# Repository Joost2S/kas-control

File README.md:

# kas-control
Kas Control is a Raspberry Pi expansion board for watering plants and checking a few more environmental variables
PCB should be correct.
Software is currently not functional. Use v2017 for basic functionality.

Features
--------
- PCB plugs straight into your rPi. rPi is powered through the PCB
- Measuring soil moisture level of up to 7 plants/containers
  - Can pump water to plant/container when moisture level is below threshold so you don't have to!
- Measuring amount of water given per channel and total
- Default 3 temperature sensors are supported by the board. Software supports infinite sensors. Make a simple breakout (connect parallel) board for more sensors.
- Light sensor for ambient light measurement.
- Float switch for use in a water container.
- Outputs:
  - 2 configurable LEDbars.
  - Standard HD44780 16x2 or 20x4 character LCD with driver kindly copied from ADAfruit.
- Network client to set the various setting and get the data.
  - Command-line only. Graph makes a Google graph html file that will open in a new tab in your browser
  - Basic encryption is implemented with openSSL
- Database
  - All sensor data is logged
  - Add a name and plant type to keep track of which plants you've grown
- 5v/12v 4A PSU PCB with INA219 power monitor. PCB files are available, haven't tested it yet.
  - 4 powerLED connectors are available for 350/500/700mA powerLED strips.
  - Power monitoring is available via INA219 ICs
  
Future Features
---------------
- Network
  - Full-fledged GUI for the network client. Probably built on Kivy.
  - rPi camera support so you can watch your plants from all over the world
- Database
  - Adding results such as plant size or harvest amount to each of your plants. Manual input only of course.
- Implement event system

Motivation
----------

I like weed. I like electronics. I like programming. Here's the result :)

Installation/requirements
-------------------------

- I use Arch Linux so only instructions for that. Actual instructions will follow later.
- RPi.GPIO
- SMBus for i2c
- spidev for SPI
- SQlite for database
- Kivy (future)

Contributors
------------

Sorry, no help wanted. This is my pet project and I want it to be just how I like it. Of Course you are welcome to use the code and pcb files as you wish.

License
-------

GNU General Public License v3.0

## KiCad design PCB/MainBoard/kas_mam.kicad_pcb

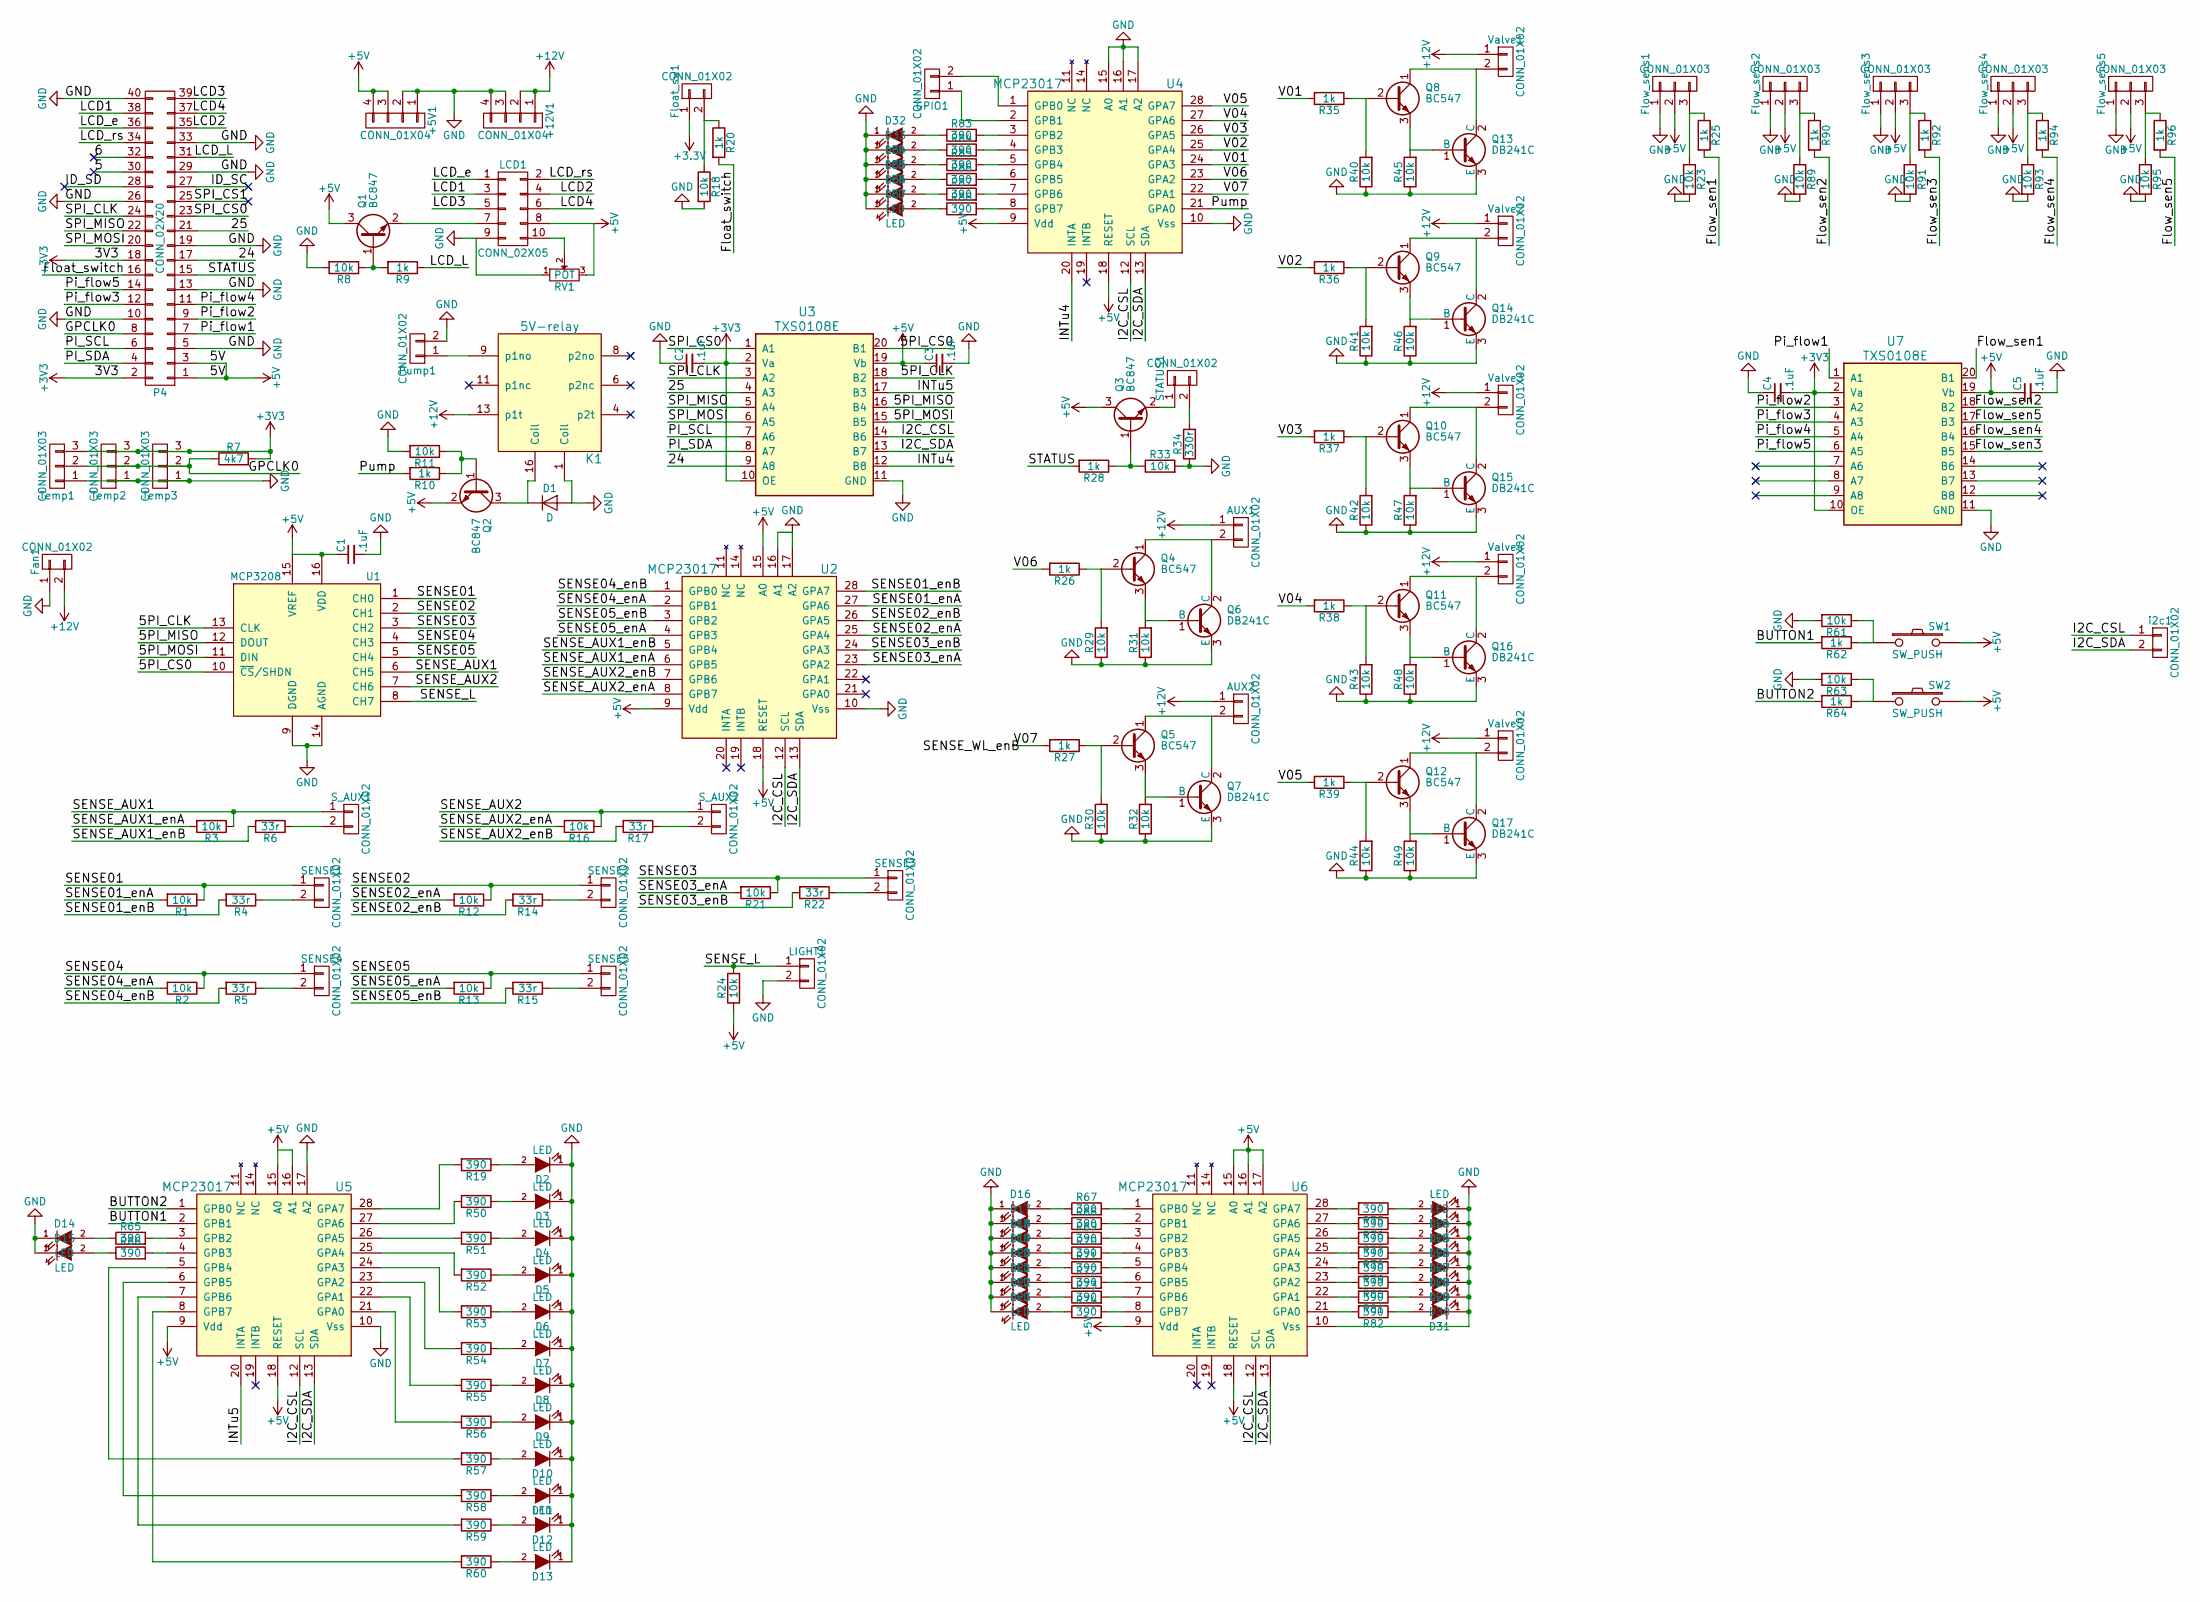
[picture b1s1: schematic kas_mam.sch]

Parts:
+5V1, +12V1: CONN_01X04; Molex_KK-6410-04_04x2.54mm_Straight
AUX1, AUX2: CONN_01X02; Molex_KK-6410-02_02x2.54mm_Straight
C1, C2, C3, C4, C5: .1uF; C_0805_HandSoldering
D1: D; D_1206
D2, D3, D4, D5, D6, D7, D8, D9, D10, D11, D12, D13, D14, D15, D16, D17, D18, D19, D20, D21, D22, D23, D24, D25, D26, D27, D28, D29, D30, D31, D32, D33, D34, D35, D36, D37: LED; LED_0805
Fan1: CONN_01X02; Molex_KK-6410-02_02x2.54mm_Straight
Float_sw1: CONN_01X02; Molex_KK-6410-02_02x2.54mm_Straight
Flow_sens1, Flow_sens2, Flow_sens3, Flow_sens4, Flow_sens5: CONN_01X03; Molex_KK-6410-03_03x2.54mm_Straight
GPIO1: CONN_01X02; Pin_Header_Straight_1x02_Pitch2.54mm
K1: 5V-relay; DIP-16_W7.62mm_Socket
LCD1: CONN_02X05; Pin_Header_Straight_2x05_Pitch2.54mm
LIGHT1: CONN_01X02; Molex_KK-6410-02_02x2.54mm_Straight
P4: CONN_02X20; Pin_Header_Straight_2x20_Pitch2.54mm
Pump1: CONN_01X02; Molex_KK-6410-02_02x2.54mm_Straight
Q1, Q2, Q3: BC847; SOT-23
Q4, Q5, Q8, Q9, Q10, Q11, Q12: BC547; TO-92_Inline_Narrow_Oval
Q6, Q7, Q13, Q14, Q15, Q16, Q17: DB241C; TO-220_Vertical
R1, R2, R3, R8, R11, R12, R13, R16, R18, R21, R23, R24, R29, R30, R31, R32, R33, R40, R41, R42, R43, R44, R45, R46, R47, R48, R49, R61, R63, R89, R91, R93, R95: 10k; R_0805_HandSoldering
R4, R5, R6, R14, R15, R17, R22: 33r; R_0805_HandSoldering
R7: 4k7; R_0805_HandSoldering
R9, R10, R20, R25, R26, R27, R28, R35, R36, R37, R38, R39, R62, R64, R90, R92, R94, R96: 1k; R_0805_HandSoldering
R19, R50, R51, R52, R53, R54, R55, R56, R57, R58, R59, R60, R65, R66, R67, R68, R69, R70, R71, R72, R73, R74, R75, R76, R77, R78, R79, R80, R81, R82, R83, R84, R85, R86, R87, R88: 390; R_0805_HandSoldering
R34: 330r; R_0805_HandSoldering
RV1: POT; Potentiometer_Trimmer_Vishay_T73YP_Horizontal
SENSE1, SENSE2, SENSE3, SENSE4, SENSE5: CONN_01X02; Molex_KK-6410-02_02x2.54mm_Straight
STATUS1: CONN_01X02; Molex_KK-6410-02_02x2.54mm_Straight
SW1, SW2: SW_PUSH; SW_PUSH_SMALL
S_AUX1, S_AUX2: CONN_01X02; Molex_KK-6410-02_02x2.54mm_Straight
Temp1, Temp2, Temp3: CONN_01X03; Molex_KK-6410-03_03x2.54mm_Straight
U1: MCP3208; DIP-16_W7.62mm_Socket
U2, U4, U5, U6: MCP23017; SOIC-28W_7.5x17.9mm_Pitch1.27mm
U3, U7: TXS0108E; SSOP-20_5.3x7.2mm_Pitch0.65mm
Valve1, Valve2, Valve3, Valve4, Valve5: CONN_01X02; Molex_KK-6410-02_02x2.54mm_Straight
i2c1: CONN_01X02; Molex_KK-6410-02_02x2.54mm_Straight

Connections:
+12V: +12V1.1, +12V1.2, AUX1.1, AUX2.1, Fan1.2, K1.13 (p1t), Valve1.1, Valve2.1, Valve3.1, Valve4.1, Valve5.1
/5PI_CLK: U1.13 (CLK), U3.18 (B2)
/5PI_MISO: U1.12 (DOUT), U3.16 (B4)
/5PI_MOSI: U1.11 (DIN), U3.15 (B5)
/24: P4.17, U3.9 (A8)
/25: P4.21, U3.4 (A3)
/BUTTON1: R62.2, U5.2 (GPB1)
/BUTTON2: R64.2, U5.1 (GPB0)
/Float_switch: P4.16, R20.2
/Flow_sen1: R25.2, U7.20 (B1)
/Flow_sen2: R90.2, U7.18 (B2)
/Flow_sen3: R92.2, U7.15 (B5)
/Flow_sen4: R94.2, U7.16 (B4)
/Flow_sen5: R96.2, U7.17 (B3)
/GPCLK0: P4.8, R7.1, Temp1.2, Temp2.2, Temp3.2
/I2C_CSL: U2.12 (SCL), U3.14 (B6), U4.12 (SCL), U5.12 (SCL), U6.12 (SCL), i2c1.1
/I2C_SDA: U2.13 (SDA), U3.13 (B7), U4.13 (SDA), U5.13 (SDA), U6.13 (SDA), i2c1.2
/INTu4: U3.12 (B8), U4.20 (INTA)
/INTu5: U3.17 (B3), U5.20 (INTA)
/LCD1: LCD1.3, P4.38
/LCD2: LCD1.4, P4.35
/LCD3: LCD1.5, P4.39
/LCD4: LCD1.6, P4.37
/LCD_L: P4.31, R9.1
/LCD_e: LCD1.1, P4.36
/LCD_rs: LCD1.2, P4.34
/PI_SCL: P4.6, U3.7 (A6)
/PI_SDA: P4.4, U3.8 (A7)
/Pi_flow1: P4.7, U7.1 (A1)
/Pi_flow2: P4.9, U7.3 (A2)
/Pi_flow3: P4.12, U7.4 (A3)
/Pi_flow4: P4.11, U7.5 (A4)
/Pi_flow5: P4.14, U7.6 (A5)
/Pump: R10.2, U4.21 (GPA0)
/SENSE01: R1.1, SENSE1.1, U1.1 (CH0)
/SENSE01_enA: R1.2, U2.27 (GPA6)
/SENSE01_enB: R4.2, U2.28 (GPA7)
/SENSE02: R12.1, SENSE2.1, U1.2 (CH1)
/SENSE02_enA: R12.2, U2.25 (GPA4)
/SENSE02_enB: R14.2, U2.26 (GPA5)
/SENSE03: R21.1, SENSE3.1, U1.3 (CH2)
/SENSE03_enA: R21.2, U2.23 (GPA2)
/SENSE03_enB: R22.2, U2.24 (GPA3)
/SENSE04: R2.1, SENSE4.1, U1.4 (CH3)
/SENSE04_enA: R2.2, U2.2 (GPB1)
/SENSE04_enB: R5.2, U2.1 (GPB0)
/SENSE05: R13.1, SENSE5.1, U1.5 (CH4)
/SENSE05_enA: R13.2, U2.4 (GPB3)
/SENSE05_enB: R15.2, U2.3 (GPB2)
/SENSE_AUX1: R3.1, S_AUX1.1, U1.6 (CH5)
/SENSE_AUX1_enA: R3.2, U2.6 (GPB5)
/SENSE_AUX1_enB: R6.2, U2.5 (GPB4)
/SENSE_AUX2: R16.1, S_AUX2.1, U1.7 (CH6)
/SENSE_AUX2_enA: R16.2, U2.8 (GPB7)
/SENSE_AUX2_enB: R17.2, U2.7 (GPB6)
/SENSE_L: LIGHT1.1, R24.2, U1.8 (CH7)
/SPI_CLK: P4.24, U3.3 (A2)
/SPI_MISO: P4.22, U3.5 (A4)
/SPI_MOSI: P4.20, U3.6 (A5)
/STATUS: P4.15, R28.2
/V01: R35.2, U4.24 (GPA3)
/V02: R36.2, U4.25 (GPA4)
/V03: R37.2, U4.26 (GPA5)
/V04: R38.2, U4.27 (GPA6)
/V05: R39.2, U4.28 (GPA7)
/V06: R26.2, U4.23 (GPA2)
/V07: R27.2, U4.22 (GPA1)
GND: +5V1.1, +5V1.2, +12V1.3, +12V1.4, C1.2, C2.1, C3.2, C4.1, C5.2, D1.2 (A), D2.1 (K), D3.1 (K), D4.1 (K), D5.1 (K), D6.1 (K), D7.1 (K), D8.1 (K), D9.1 (K), D10.1 (K), D11.1 (K), D12.1 (K), D13.1 (K), D14.1 (K), D15.1 (K), D16.1 (K), D17.1 (K), D18.1 (K), D19.1 (K), D20.1 (K), D21.1 (K), D22.1 (K), D23.1 (K), D24.1 (K), D25.1 (K), D26.1 (K), D27.1 (K), D28.1 (K), D29.1 (K), D30.1 (K), D31.1 (K), D32.1 (K), D33.1 (K), D34.1 (K), D35.1 (K), D36.1 (K), D37.1 (K), Fan1.1, Flow_sens1.1, Flow_sens2.1, Flow_sens3.1, Flow_sens4.1, Flow_sens5.1, K1.1 (Coil), LCD1.9, LIGHT1.2, P4.5, P4.10, P4.13, P4.19, P4.26, P4.29, P4.33, P4.40, Pump1.2, Q6.3 (E), Q7.3 (E), Q13.3 (E), Q14.3 (E), Q15.3 (E), Q16.3 (E), Q17.3 (E), R8.2, R11.2, R18.2, R23.2, R29.1, R30.1, R31.1, R32.1, R33.2, R34.1, R40.1, R41.1, R42.1, R43.1, R44.1, R45.1, R46.1, R47.1, R48.1, R49.1, R61.2, R63.2, R89.2, R91.2, R93.2, R95.2, RV1.1, Temp1.1, Temp2.1, Temp3.1, U1.9 (DGND), U1.14 (AGND), U2.10 (Vss), U2.16 (A1), U2.17 (A2), U3.11 (GND), U4.10 (Vss), U4.15 (A0), U4.16 (A1), U4.17 (A2), U5.10 (Vss), U5.17 (A2), U6.10 (Vss), U7.11 (GND)
unnamed: AUX1.2, Q4.1 (C), Q6.2 (C)
unnamed: AUX2.2, Q5.1 (C), Q7.2 (C)
unnamed: D1.1 (K), K1.16 (Coil), Q2.3 (C)
unnamed: D2.2 (A), R19.1
unnamed: D3.2 (A), R50.1
unnamed: D4.2 (A), R51.1
unnamed: D5.2 (A), R52.1
unnamed: D6.2 (A), R53.1
unnamed: D7.2 (A), R54.1
unnamed: D8.2 (A), R55.1
unnamed: D9.2 (A), R56.1
unnamed: D10.2 (A), R57.1
unnamed: D11.2 (A), R58.1
unnamed: D12.2 (A), R59.1
unnamed: D13.2 (A), R60.1
unnamed: D14.2 (A), R65.1
unnamed: D15.2 (A), R66.1
unnamed: D16.2 (A), R67.1
unnamed: D17.2 (A), R68.1
unnamed: D18.2 (A), R69.1
unnamed: D19.2 (A), R70.1
unnamed: D20.2 (A), R71.1
unnamed: D21.2 (A), R72.1
unnamed: D22.2 (A), R73.1
unnamed: D23.2 (A), R74.1
unnamed: D24.2 (A), R75.1
unnamed: D25.2 (A), R76.1
unnamed: D26.2 (A), R77.1
unnamed: D27.2 (A), R78.1
unnamed: D28.2 (A), R79.1
unnamed: D29.2 (A), R80.1
unnamed: D30.2 (A), R81.1
unnamed: D31.2 (A), R82.1
unnamed: D32.2 (A), R83.1
unnamed: D33.2 (A), R84.1
unnamed: D34.2 (A), R85.1
unnamed: D35.2 (A), R86.1
unnamed: D36.2 (A), R87.1
unnamed: D37.2 (A), R88.1
unnamed: Float_sw1.2, R18.1, R20.1
unnamed: Flow_sens1.3, R23.1, R25.1
unnamed: Flow_sens2.3, R89.1, R90.1
unnamed: Flow_sens3.3, R91.1, R92.1
unnamed: Flow_sens4.3, R93.1, R94.1
unnamed: Flow_sens5.3, R95.1, R96.1
unnamed: GPIO1.1, U4.2 (GPB1)
unnamed: GPIO1.2, U4.1 (GPB0)
unnamed: K1.9 (p1no), Pump1.1
unnamed: LCD1.7, Q1.2 (E)
unnamed: LCD1.10, RV1.2
unnamed: Q1.1 (B), R8.1, R9.2
unnamed: Q2.1 (B), R10.1, R11.1
unnamed: Q3.1 (B), R28.1, R33.1
unnamed: Q3.2 (E), STATUS1.1
unnamed: Q4.2 (B), R26.1, R29.2
unnamed: Q4.3 (E), Q6.1 (B), R31.2
unnamed: Q5.2 (B), R27.1, R30.2
unnamed: Q5.3 (E), Q7.1 (B), R32.2
unnamed: Q8.2 (B), R35.1, R40.2
unnamed: Q9.2 (B), R36.1, R41.2
unnamed: Q10.1 (C), Q15.2 (C), Valve3.2
unnamed: Q10.2 (B), R37.1, R42.2
unnamed: Q10.3 (E), Q15.1 (B), R47.2
unnamed: Q11.1 (C), Q16.2 (C), Valve4.2
unnamed: Q11.2 (B), R38.1, R43.2
unnamed: Q11.3 (E), Q16.1 (B), R48.2
unnamed: Q12.1 (C), Q17.2 (C), Valve5.2
unnamed: Q12.2 (B), R39.1, R44.2
unnamed: Q12.3 (E), Q17.1 (B), R49.2
unnamed: Q8.3 (E), Q13.1 (B), R45.2
unnamed: Q8.1 (C), Q13.2 (C), Valve1.2
unnamed: Q9.3 (E), Q14.1 (B), R46.2
unnamed: Q9.1 (C), Q14.2 (C), Valve2.2
unnamed: R4.1, SENSE1.2
unnamed: R5.1, SENSE4.2
unnamed: R6.1, S_AUX1.2
unnamed: R14.1, SENSE2.2
unnamed: R15.1, SENSE5.2
unnamed: R17.1, S_AUX2.2
unnamed: R19.2, U5.28 (GPA7)
unnamed: R22.1, SENSE3.2
unnamed: R34.2, STATUS1.2
unnamed: R50.2, U5.27 (GPA6)
unnamed: R51.2, U5.26 (GPA5)
unnamed: R52.2, U5.25 (GPA4)
unnamed: R53.2, U5.24 (GPA3)
unnamed: R54.2, U5.23 (GPA2)
unnamed: R55.2, U5.22 (GPA1)
unnamed: R56.2, U5.21 (GPA0)
unnamed: R57.2, U5.5 (GPB4)
unnamed: R58.2, U5.6 (GPB5)
unnamed: R59.2, U5.7 (GPB6)
unnamed: R60.2, U5.8 (GPB7)
unnamed: R61.1, R62.1, SW1.1
unnamed: R63.1, R64.1, SW2.1
unnamed: R65.2, U5.3 (GPB2)
unnamed: R66.2, U5.4 (GPB3)
unnamed: R67.2, U6.1 (GPB0)
unnamed: R68.2, U6.2 (GPB1)
unnamed: R69.2, U6.3 (GPB2)
unnamed: R70.2, U6.4 (GPB3)
unnamed: R71.2, U6.5 (GPB4)
unnamed: R72.2, U6.6 (GPB5)
unnamed: R73.2, U6.7 (GPB6)
unnamed: R74.2, U6.8 (GPB7)
unnamed: R75.2, U6.28 (GPA7)
unnamed: R76.2, U6.27 (GPA6)
unnamed: R77.2, U6.26 (GPA5)
unnamed: R78.2, U6.25 (GPA4)
unnamed: R79.2, U6.24 (GPA3)
unnamed: R80.2, U6.23 (GPA2)
unnamed: R81.2, U6.22 (GPA1)
unnamed: R82.2, U6.21 (GPA0)
unnamed: R83.2, U4.3 (GPB2)
unnamed: R84.2, U4.4 (GPB3)
unnamed: R85.2, U4.5 (GPB4)
unnamed: R86.2, U4.6 (GPB5)
unnamed: R87.2, U4.7 (GPB6)
unnamed: R88.2, U4.8 (GPB7)

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
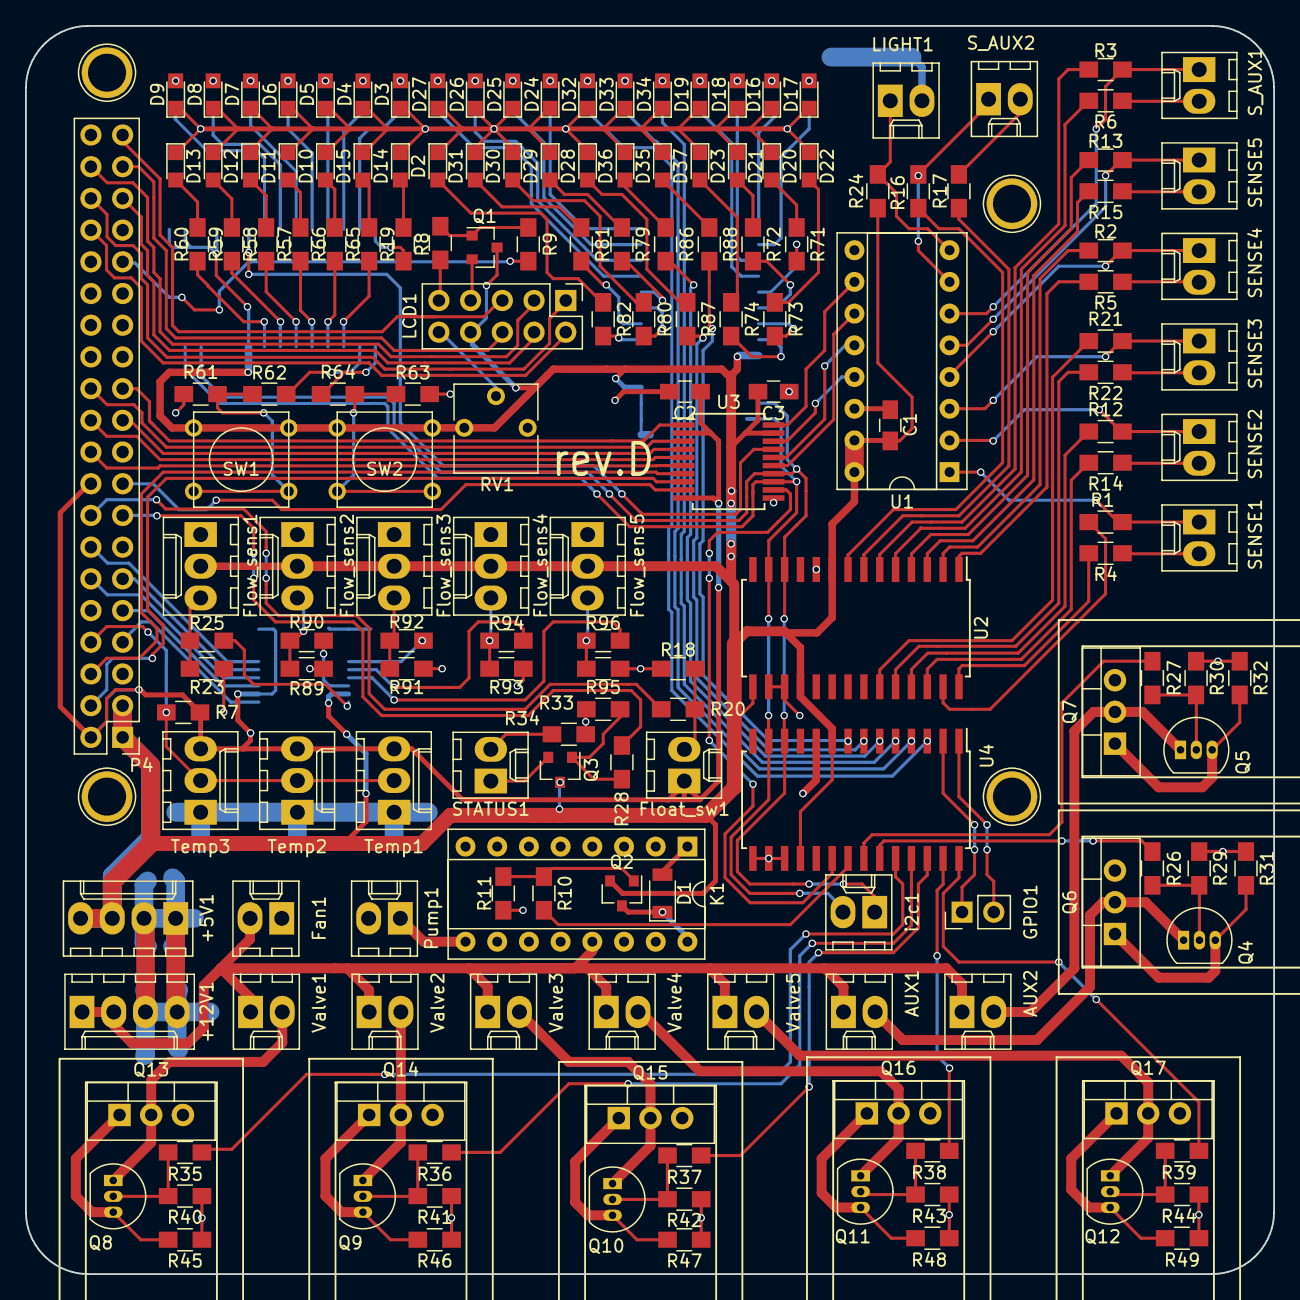
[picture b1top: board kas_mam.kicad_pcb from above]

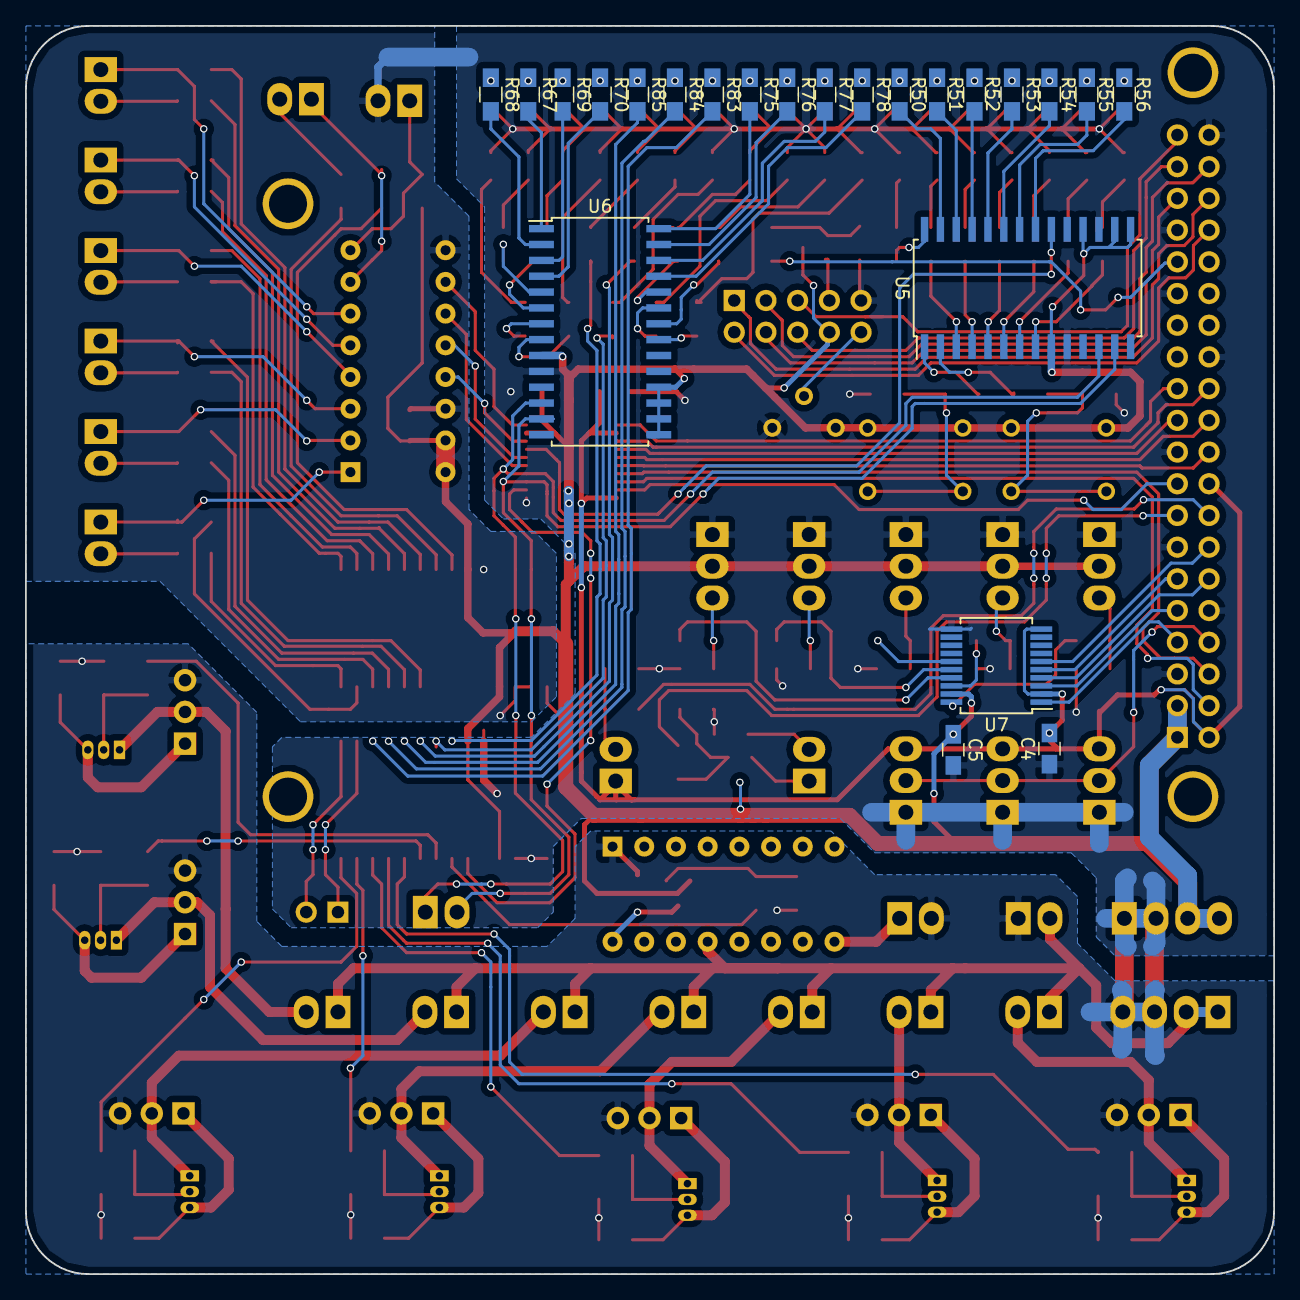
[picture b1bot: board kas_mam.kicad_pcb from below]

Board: 2 copper layers, 100.0 x 100.0 mm, 199 parts (23 on the bottom side), 191 nets.

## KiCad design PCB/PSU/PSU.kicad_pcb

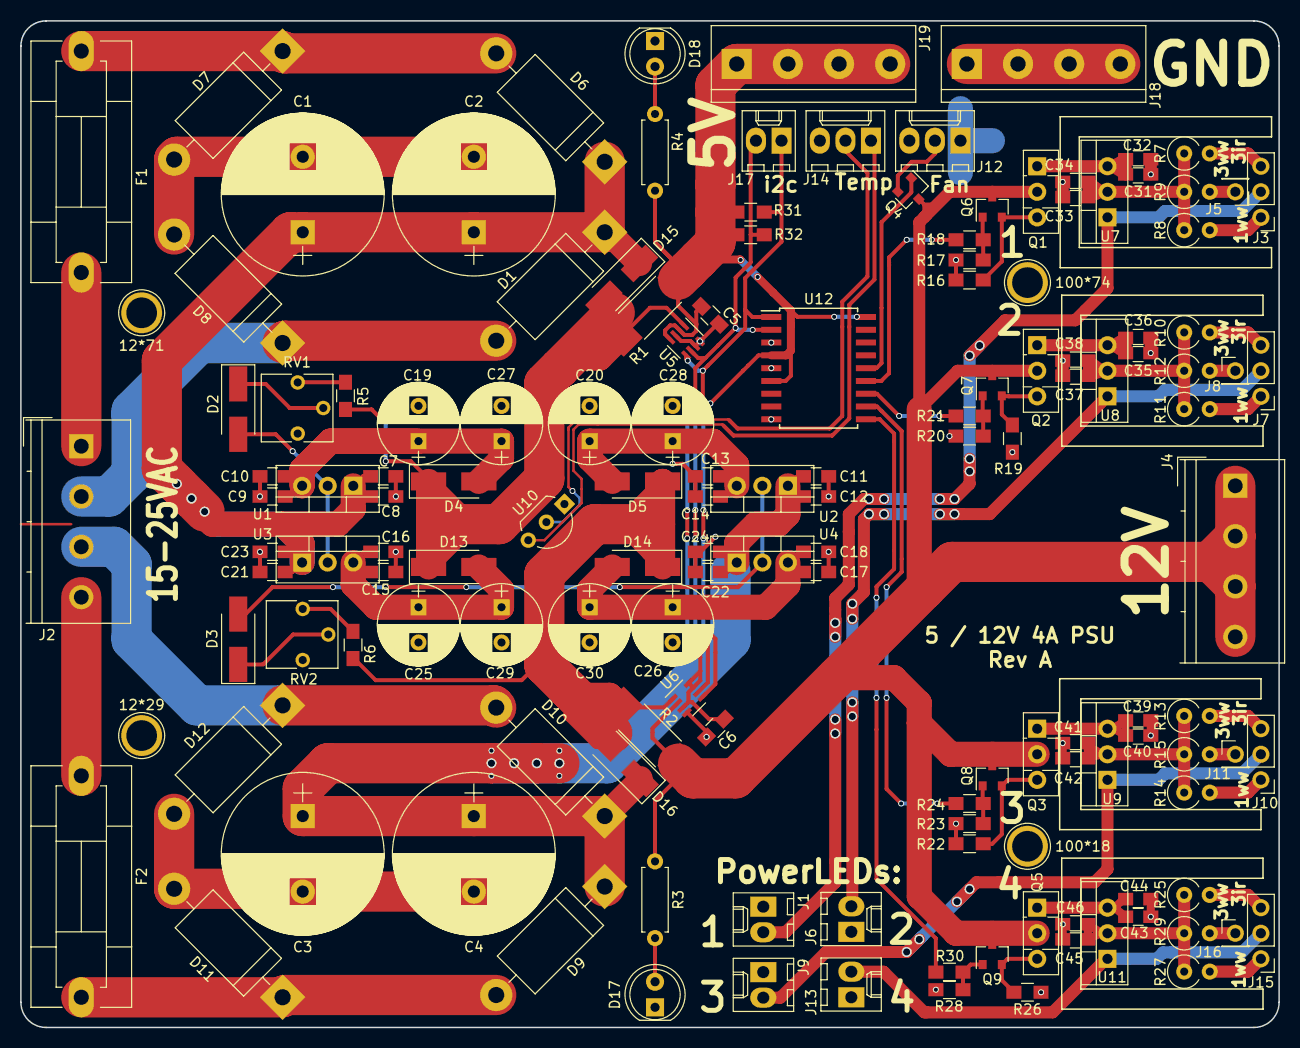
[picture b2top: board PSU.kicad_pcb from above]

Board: 2 copper layers, 125.0 x 100.0 mm, 144 parts (0 on the bottom side), 67 nets.

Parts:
12*29, 12*71, 100*18, 100*74: 1pin
C1, C2, C3, C4: 2.2mF; CP_Radial_D16.0mm_P7.50mm
C5, C6, C8, C9, C12, C14, C16, C18, C23, C24, C32, C33, C36, C37, C40, C41, C44, C45: .1uF; C_0805_HandSoldering
C7, C10, C11, C13, C15, C17, C21, C22, C31, C34, C35, C38, C39, C42, C43, C46: .01uF; C_0805_HandSoldering
C19, C20, C25, C26, C27, C28, C29, C30: 470uF; CP_Radial_D8.0mm_P3.50mm
D1, D6, D7, D9, D10, D11, D12: SR560; D_DO-201AD_P15.24mm_Horizontal
D2, D3, D4, D5, D13, D14, D15, D16: SS56; D_SMA_Handsoldering
D8: SR560; D_DO-201_P15.24mm_Horizontal
D17: Yellow; LED_D5.0mm
D18: RED; LED_D5.0mm
F1, F2: FUSE; Fuseholder5x20_horiz_SemiClosed_Casing10x25mm
J1, J6, J9, J13, J17: Conn_01x02; Molex_KK-6410-02_02x2.54mm_Straight
J2, J4: Conn_01x04; TerminalBlock_Philmore_TB13x_04x5mm_Straight
J3, J7, J10, J15: Conn_01x03; Pin_Header_Straight_1x03_Pitch2.54mm
J5, J8, J11, J16: Conn_01x01; Pin_Header_Straight_1x01_Pitch2.54mm
J12: Conn_01x02; Molex_KK-6410-03_03x2.54mm_Straight
J14: Conn_01x03; Molex_KK-6410-03_03x2.54mm_Straight
J18, J19: Conn_01x04; TerminalBlock_bornier-4_P5.08mm
Q1, Q2, Q3, Q5: BD139; TO-126_Vertical
Q4, Q6, Q7, Q8, Q9: BC847; SOT-23
R1, R2: 0R04; R_2512_HandSoldering
R3: 680; R_Axial_DIN0207_L6.3mm_D2.5mm_P7.62mm_Horizontal
R4: 270; R_Axial_DIN0207_L6.3mm_D2.5mm_P7.62mm_Horizontal
R5, R6, R18, R21, R24, R30: 1k; R_0805_HandSoldering
R7, R10, R13, R25: 2R7; R_Axial_DIN0309_L9.0mm_D3.2mm_P2.54mm_Vertical
R8, R11, R14, R27: 3R9; R_Axial_DIN0309_L9.0mm_D3.2mm_P2.54mm_Vertical
R9, R12, R15, R29: 1R8; R_Axial_DIN0309_L9.0mm_D3.2mm_P2.54mm_Vertical
R16, R17, R19, R20, R22, R23, R26, R28: 10k; R_0805_HandSoldering
R31, R32: 2k2; R_0805_HandSoldering
RV1, RV2: 100R; Potentiometer_Trimmer_Vishay_T73YP_Horizontal
U1, U3: LM7805CT; TO-220_Vertical
U2, U4: LM7812CT; TO-220_Vertical
U5, U6: INA219; SOT-23-8
U7, U8, U9, U11: LM317_3PinPackage; TO-220_Vertical
U10: DS18B20; TO-92_Inline_Wide
U12: MCP23008; SOIC-18W_7.5x11.6mm_Pitch1.27mm

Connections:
+5V: C5.2, C6.1, J19.1, J19.2, J19.3, J19.4, R1.2, R4.2, R31.1, R32.2, U5.2, U5.4, U6.3, U6.7, U6.8, U12.4, U12.6, U12.18
+12V: J4.1, J4.2, J4.3, J4.4, Q1.2, Q2.2, Q3.2, Q4.3, Q5.2, Q6.3, Q7.3, Q8.3, Q9.3, R2.2, R3.1, U6.2
/3.3v: J14.1, U10.3
/5Vadj: D2.2, U1.2, U3.2
/5Vout: D4.1, D13.1, D15.2, R1.1, R5.1, U5.1
/12Vadj: D3.2, U2.2, U4.2
/12Vout: D5.1, D14.1, D16.2, R2.1, R6.1, U6.1
/16.5VDC1: C1.1, C2.1, C7.2, C8.2, C21.2, C23.2, D1.1, D6.1, D15.1, U1.1, U3.1
/16.5VDC2: C3.1, C4.1, C11.2, C12.2, C22.2, C24.2, D9.1, D10.1, D16.1, U2.1, U4.1
/18VAC1: F1.1, J2.1
/18VAC2: D1.2, D8.1, J2.2
/18VAC3: D10.2, D12.1, J2.3
/18VAC4: F2.1, J2.4
/CSL: J17.1, R31.2, U5.5, U6.5, U12.1
/FAN: Q4.1, U12.14
/LED1: R18.1, U12.13
/LED2: R21.1, U12.12
/LED3: R24.1, U12.11
/LED4: R30.1, U12.10
/SDA: J17.2, R32.1, U5.6, U6.6, U12.2
/Tdata: J14.2, U10.2
GND: C1.2, C2.2, C3.2, C4.2, C5.1, C6.2, C7.1, C8.1, C9.1, C10.1, C11.1, C12.1, C13.1, C14.1, C15.1, C16.1, C17.1, C18.1, C19.2, C20.2, C21.1, C22.1, C23.1, C24.1, C25.2, C26.2, C27.2, C28.2, C29.2, C30.2, C31.2, C32.2, C33.2, C34.2, C35.2, C36.2, C37.2, C38.2, C39.2, C40.2, C41.2, C42.2, C43.2, C44.2, C45.2, C46.2, D7.2, D8.2, D11.2, D12.2, D17.1, D18.1, J1.1, J6.1, J9.1, J12.1, J13.1, J14.3, J18.1, J18.2, J18.3, J18.4, R16.1, R17.1, R19.1, R20.1, R22.1, R23.1, R26.1, R28.1, RV1.1, RV2.1, U5.3, U5.7, U5.8, U6.4, U10.1, U12.3, U12.5, U12.9
unnamed: C9.2, C10.2, C19.1, C27.1, D4.2, U1.3
unnamed: C13.2, C14.2, C20.1, C28.1, D5.2, U2.3
unnamed: C15.2, C16.2, C25.1, C29.1, D13.2, U3.3
unnamed: C17.2, C18.2, C26.1, C30.1, D14.2, U4.3
unnamed: C31.1, C32.1, Q1.1, U7.3
unnamed: C33.1, C34.1, R7.1, R8.1, R9.1, U7.2
unnamed: C35.1, C36.1, Q2.1, U8.3
unnamed: C37.1, C38.1, R10.1, R11.1, R12.1, U8.2
unnamed: C39.1, C40.1, Q3.1, U9.3
unnamed: C41.1, C42.1, R13.1, R14.1, R15.1, U9.2
unnamed: C43.1, C44.1, Q5.1, U11.3
unnamed: C45.1, C46.1, R25.1, R27.1, R29.1, U11.2
unnamed: D2.1, RV1.2
unnamed: D3.1, RV2.2
unnamed: D6.2, D7.1, F1.2
unnamed: D9.2, D11.1, F2.2
unnamed: D17.2, R3.2
unnamed: D18.2, R4.1
unnamed: J1.2, J3.2, U7.1
unnamed: J3.1, R8.2
unnamed: J3.3, R7.2
unnamed: J5.1, R9.2
unnamed: J6.2, J7.2, U8.1
unnamed: J7.1, R11.2
unnamed: J7.3, R10.2
unnamed: J8.1, R12.2
unnamed: J10.1, R14.2
unnamed: J9.2, J10.2, U9.1
unnamed: J10.3, R13.2
unnamed: J11.1, R15.2
unnamed: J12.2, Q4.2
unnamed: J13.2, J15.2, U11.1
unnamed: J15.1, R27.2
unnamed: J15.3, R25.2
unnamed: J16.1, R29.2
unnamed: Q1.3, Q6.2, R16.2
unnamed: Q2.3, Q7.2, R19.2
unnamed: Q3.3, Q8.2, R22.2
unnamed: Q5.3, Q9.2, R26.2
unnamed: Q6.1, R17.2, R18.2
unnamed: Q7.1, R20.2, R21.2
unnamed: Q8.1, R23.2, R24.2
unnamed: Q9.1, R28.2, R30.2
unnamed: R5.2, RV1.3
unnamed: R6.2, RV2.3

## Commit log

2017-07-28 Adding PCB files
    This version doesn't have SPI working yet, so no analog data.
2017-07-28 Added image of front layer
2018-01-05 RevC v 1.1
    Fis for PCB. Should work now.
2018-01-05 v2016
    First version of software that worked with simple hardware.
2018-01-06 v2017
    Software for the revC 1.1 version of the board. Not nearly all features are suppoerted.
2018-01-08 README update
2018-01-09 v2018-01-08
    Code is still work in progress. Won't run.
2018-01-10 Update 2018-01-09
    Still not working.
2018-01-11 Update 2018-01-10
    mostly some db and network stuff
    data network command done
    working on water network command
2018-01-22 Update 2018-01-21
2018-01-28 Update 2018-01-27
    Updated mcp23017 driver to also support mcp23008. Still need to test it.
    Some more work was done on the ina219 driver. Lots more to be done.
2018-01-30 Update 2018-01-29
    Mostly got the INA210 driver closer to a working state.
2018-01-31 Update 2018-01-30
    Some minor updates.
2018-02-01 Update 2018-01-31
    Removed some outdated code.
    Added netcommand "container history".
2018-02-02 Update 2018-02-01
2018-02-10 Update 2018-02-09
    - Added support for MCP3x04, 'cause.
    - Added preliminary and non-functional support for HD44780 and LEDbars. Lots of code to be changed in the last one.
    - Other small updates.
2018-02-11 PSU rev A PCB
    First version of my 5v / 12v 4A PSU with powermonitoring and support for some powerLEDs
2018-02-11 Update 2018-02-09
    Plenty of large and small improvements. Not much closer to a working version :p
2018-02-12 Update 2018-02-11
    Mostly added code for powerLEDs.
    Added some code for toggleable fan.
    Some other small updates.
2018-02-14 Update 2018-02-13
    Initializing checks for the databse are done I think.
    Getting closer to a working version.
2018-02-15 Update 2018-02-14
    Added some descriptions to the methods in hwControl.
2018-02-16 Update 2018-02-15
    Just some more misc fixes and updates.
2018-02-17 Update 2018-02-16
    Added some code for hte lEDbars.
2018-03-02 PSU PCB rev A final
2018-03-02 Main Board rev D
2018-03-03 Update 2018-03-02
    Some improvements, better integration of LEDbars and LCD.
2018-03-04 Update 2018-03-03
    Moved netCommand.getTabs method to globstuff so it is available to all systems.
    Started on an improved power management system based on a priority queue.
2018-03-04 Small cosmetic update
2018-03-05 Update 2018-03-04
    Monitor method now collects data in a dict instead of a simple list.
    Fixed MCP230xx driver.
2018-03-11 Update 2018-03-10
    Wokring code for LCD and LEDbars
    Removed a bunch of old code.
    Planty of other small changes.
2018-03-13 README
    Updated readme file to reflect the implementation of the LCD and LEDbars.
2018-03-17 Update 2018-03-16
    Mostly style updates and simple fixes.
2018-04-02 Update 2018-04-01
2018-05-22 Update 2018-05-21
    Added powerManager.
    introduced UUIDs to the mcp320xx drivers for exclusive pin usage.
    Changed sensorSetup file to JSON.
    Lots of misc fixes and updates.
2018-07-09 Update 2018-07-09
    Various changes
2019-04-24 Update .gitignore
    .gitignore update
2019-04-28 Update 2018-07-09
    Reworked the file strucure
2019-05-15 Update 2019-05-15
2019-05-18 Update 2019-05-17
2019-05-19 Update 2019-05-19
2019-05-20 Update 2019-05-20
2019-05-26 Update 2019-05-26
